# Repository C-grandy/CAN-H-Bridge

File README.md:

# CAN-H-Bridge
A CAN Bus controlled H-Bridge motor driver designed for 12V, 10-20A brushed motors with encoders. Features a Atmel Atmega328 MCU along with a MCP2515 CAN controller for compatability with Arduino or standalone AVR C. 
NOTE: This design should not be used as is, it has a few design flaws as it was a proof of concept that was never developed further. 
## Circuit Overview
The design has two major parts, the controls and the H-Bridge motor driver. 
### Controls
The heart of the control system is the Atmega328 MCU. This MCU communicates over CAN for connectivity to other devices along with sending the appropriate PWM and enable signals to the H-bridge driver. It has connectors for a 2 pin quadrature encoder, specifically designed with GoBilda Yellow Jacket gear motors in mind. 

### Driver
The driver features 2 IRS2104's half-bridge gate drivers to drive the IRF3205 MOSFETS. This is a standard H-bridge setup, with adequete protection for expected loads. 
NOTE: This circuit uses a external 12V refrence for the IRS2104 input voltage, do not exceed 12V on board VCC or the driver might not work correctly. This is a major design flaw in the circuit as it should include a isolated supply that is refrenced off of VCC. 

## PCB Layout:
This board is a 2 layer stackup, with very basic PCB design rules followed. The overall design of the PCB is lacking, the traces are not properly sized for the loads at hand and a lack of copper pours makes this a elementary design. Even with these shortcomings, the PCB works as expected, but in long tests proved it needed refinement. 

Front: 

Back: 

### 3D Render: 

Front:

Back:

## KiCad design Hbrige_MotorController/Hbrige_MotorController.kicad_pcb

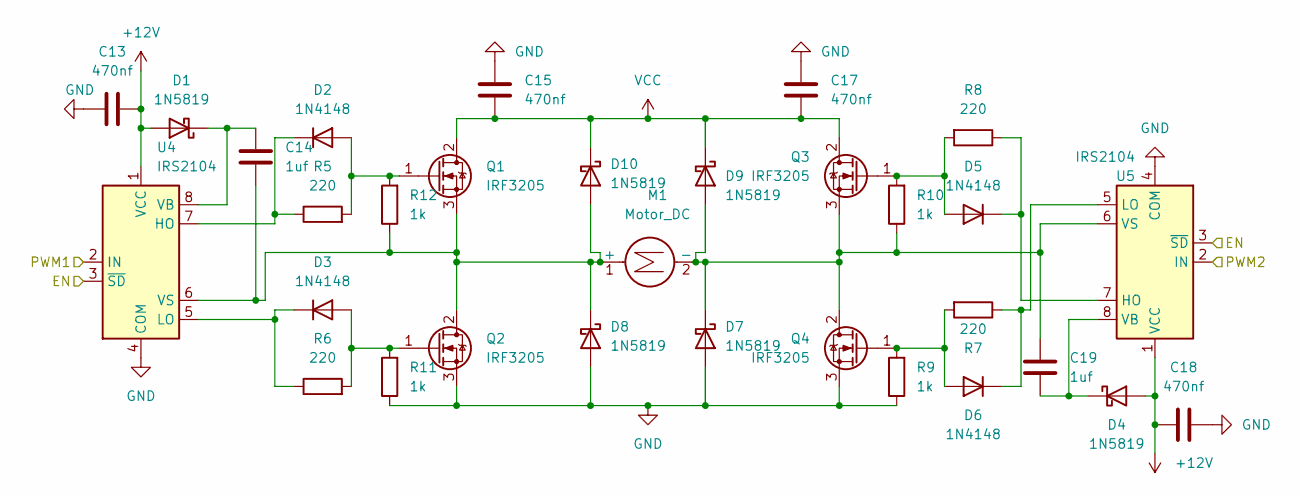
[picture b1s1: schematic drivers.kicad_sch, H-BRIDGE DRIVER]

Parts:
C13, C15, C17, C18: 470nf; C_0603_1608Metric_Pad1.08x0.95mm_HandSolder
C14, C19: 1uf; C_0603_1608Metric_Pad1.08x0.95mm_HandSolder
D1, D4, D7, D8, D9, D10: 1N5819; D_SOD-123
D2, D3, D5, D6: 1N4148; D_SOD-523
M1: Motor_DC; TerminalBlock_Altech_AK300-2_P5.00mm
Q1, Q2, Q3, Q4: IRF3205; TO-220-3_Horizontal_TabDown
R5, R6, R7, R8: 220; R_0603_1608Metric_Pad0.98x0.95mm_HandSolder
R9, R10, R11, R12: 1k; R_0603_1608Metric_Pad0.98x0.95mm_HandSolder
U4, U5: IRS2104; SOIC-8_3.9x4.9mm_P1.27mm

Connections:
+12V: C13.1, C18.2, D1.2 (A), D4.2 (A), U4.1 (VCC), U5.1 (VCC); also elsewhere on the board
/Controls/EN: U4.3 (~SD), U5.3 (~SD); also elsewhere on the board
/Controls/PWM1: U4.2 (IN); also elsewhere on the board
/Controls/PWM2: U5.2 (IN); also elsewhere on the board
GND: C13.2, C15.2, C17.2, C18.1, D7.2 (A), D8.2 (A), Q2.3 (S), Q4.3 (S), R9.1, R11.1, U4.4 (COM), U5.4 (COM); also elsewhere on the board
unnamed: C14.1, D1.1 (K), U4.8 (VB)
unnamed: C14.2, D8.1 (K), D10.2 (A), M1.1 (+), Q1.3 (S), Q2.2 (D), R12.1, U4.6 (VS)
unnamed: C19.1, D4.1 (K), U5.8 (VB)
unnamed: C19.2, D7.1 (K), D9.2 (A), M1.2 (-), Q3.3 (S), Q4.2 (D), R10.1, U5.6 (VS)
unnamed: D2.1 (K), R5.1, U4.7 (HO)
unnamed: D2.2 (A), Q1.1 (G), R5.2, R12.2
unnamed: D3.1 (K), R6.1, U4.5 (LO)
unnamed: D3.2 (A), Q2.1 (G), R6.2, R11.2
unnamed: D5.1 (K), R8.1, U5.7 (HO)
unnamed: D5.2 (A), Q3.1 (G), R8.2, R10.2
unnamed: D6.1 (K), R7.1, U5.5 (LO)
unnamed: D6.2 (A), Q4.1 (G), R7.2, R9.2
VCC: C15.1, C17.1, D9.1 (K), D10.1 (K), Q1.2 (D), Q3.2 (D); also elsewhere on the board

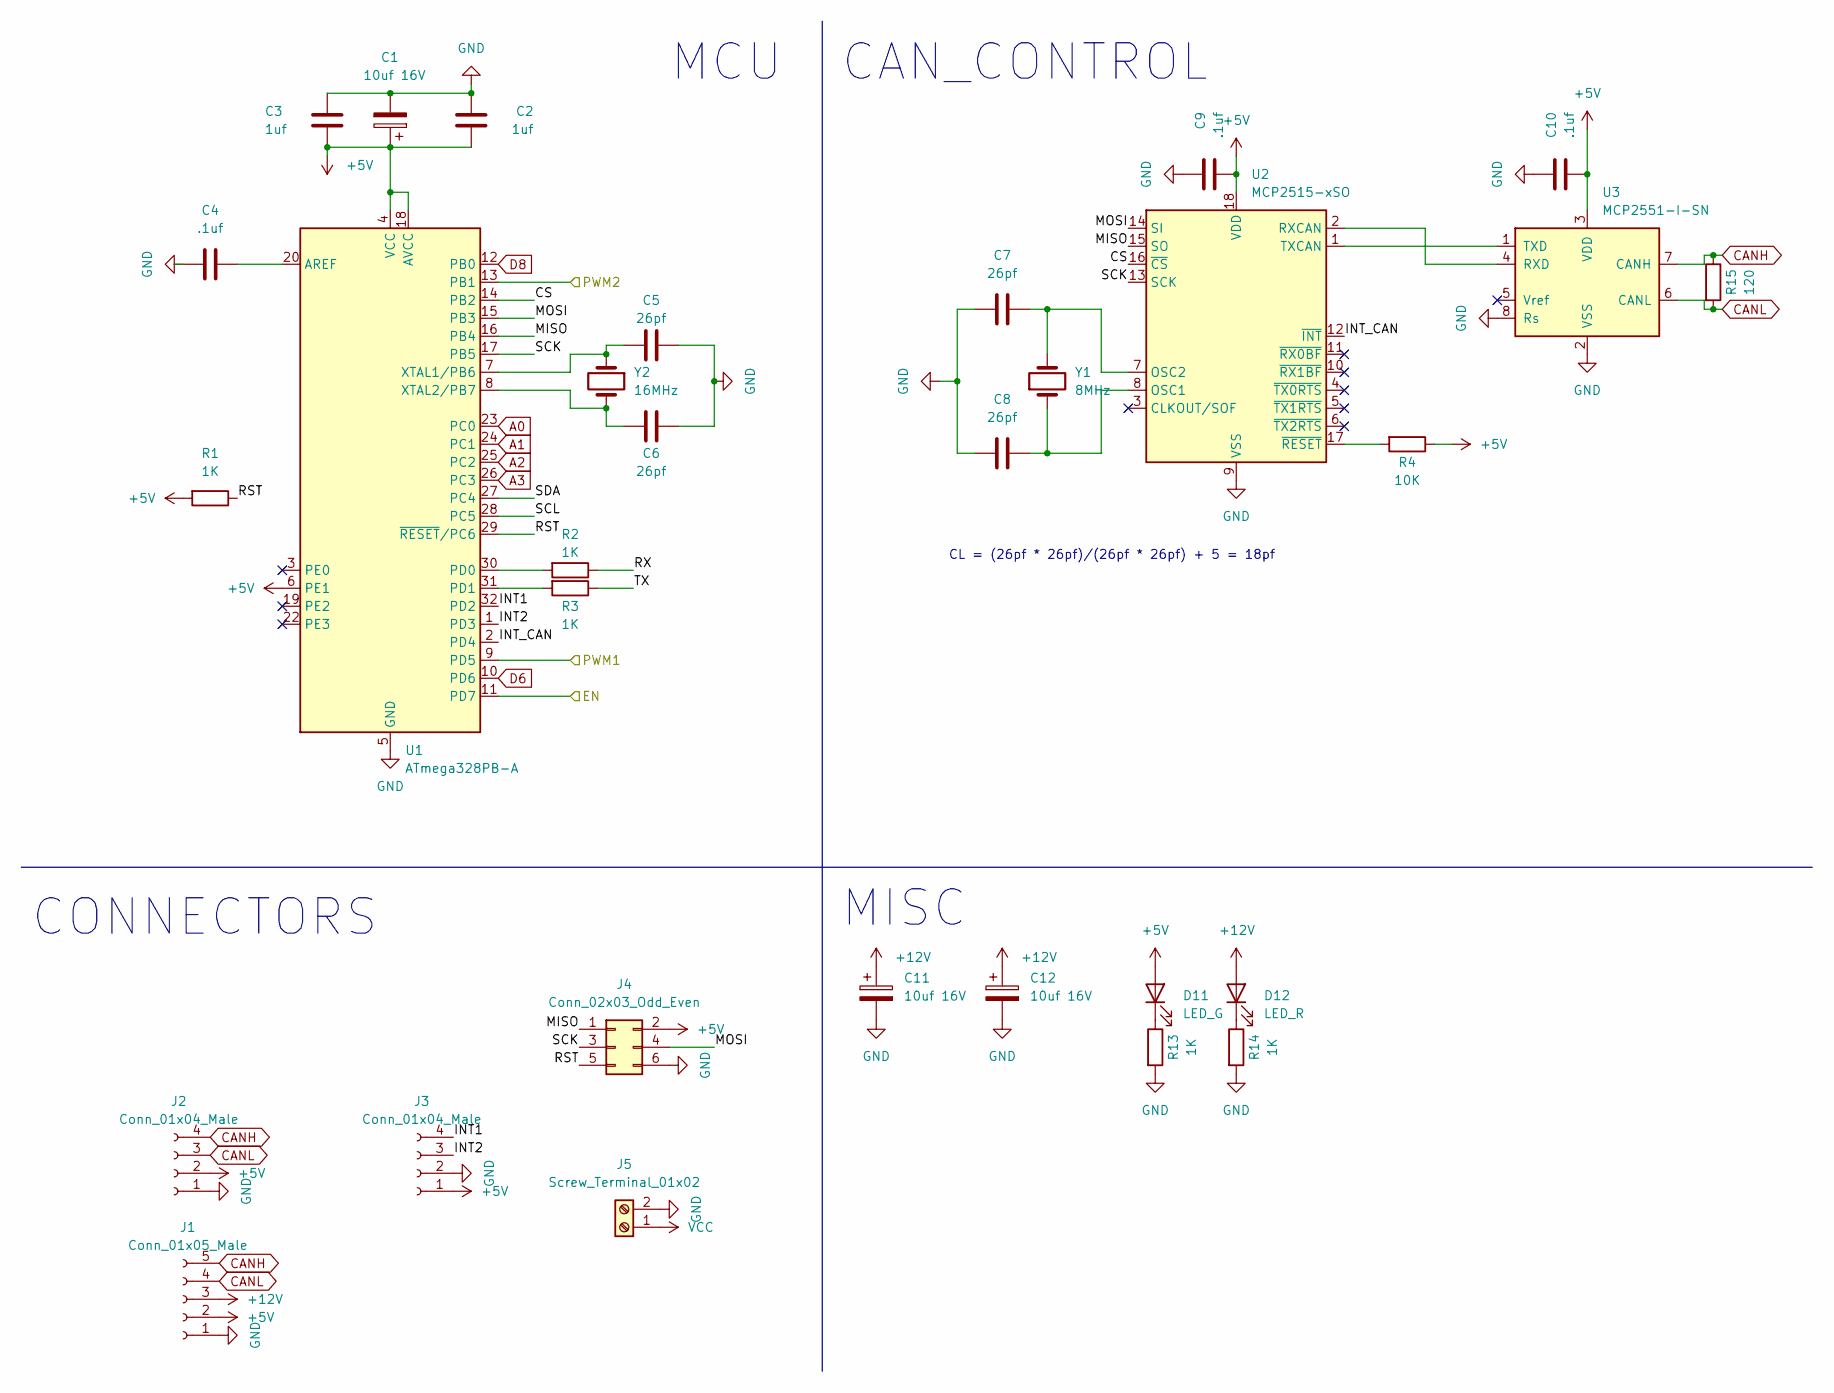
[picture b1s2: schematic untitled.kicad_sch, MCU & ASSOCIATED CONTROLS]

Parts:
C1, C11, C12: 10uf 16V; CP_Radial_D5.0mm_P2.00mm
C2, C3: 1uf; C_0603_1608Metric_Pad1.08x0.95mm_HandSolder
C4, C9, C10: .1uf; C_0603_1608Metric_Pad1.08x0.95mm_HandSolder
C5, C6, C7, C8: 26pf; C_0603_1608Metric_Pad1.08x0.95mm_HandSolder
D11: LED_G; LED_0603_1608Metric_Pad1.05x0.95mm_HandSolder
D12: LED_R; LED_0603_1608Metric_Pad1.05x0.95mm_HandSolder
J1: Conn_01x05_Male; JST_XH_B5B-XH-A_1x05_P2.50mm_Vertical
J2, J3: Conn_01x04_Male; JST_XA_B04B-XASK-1-A_1x04_P2.50mm_Vertical
J4: Conn_02x03_Odd_Even; PinHeader_2x03_P2.54mm_Vertical
J5: Screw_Terminal_01x02; TerminalBlock_Altech_AK300-2_P5.00mm
R1, R2, R3, R13, R14: 1K; R_0603_1608Metric_Pad0.98x0.95mm_HandSolder
R4: 10K; R_0603_1608Metric_Pad0.98x0.95mm_HandSolder
R15: 120; R_0603_1608Metric_Pad0.98x0.95mm_HandSolder
U1: ATmega328PB-A; TQFP-32_7x7mm_P0.8mm
U2: MCP2515-xSO; SOIC-18W_7.5x11.6mm_P1.27mm
U3: MCP2551-I-SN; SOIC-8_3.9x4.9mm_P1.27mm
Y1: 8MHz; Crystal_SMD_5032-2Pin_5.0x3.2mm
Y2: 16MHz; Crystal_SMD_5032-2Pin_5.0x3.2mm

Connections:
+5V: C1.1, C2.2, C3.1, C9.2, C10.2, D11.2 (A), J1.2, J2.2, J3.1, J4.2, R1.2, R4.1, U1.4 (VCC), U1.6 (PE1), U1.18 (AVCC), U2.18 (VDD), U3.3 (VDD)
+12V: C11.1, C12.1, D12.2 (A), J1.3; also elsewhere on the board
/Controls/CS: U1.14 (PB2), U2.16 (~CS)
/Controls/EN: U1.11 (PD7); also elsewhere on the board
/Controls/INT1: J3.4, U1.32 (PD2)
/Controls/INT2: J3.3, U1.1 (PD3)
/Controls/INT_CAN: U1.2 (PD4), U2.12 (~INT)
/Controls/MISO: J4.1, U1.16 (PB4), U2.15 (SO)
/Controls/MOSI: J4.4, U1.15 (PB3), U2.14 (SI)
/Controls/PWM1: U1.9 (PD5); also elsewhere on the board
/Controls/PWM2: U1.13 (PB1); also elsewhere on the board
/Controls/RST: J4.5, R1.1, U1.29 (~RESET/PC6)
/Controls/RX: R2.1
/Controls/SCK: J4.3, U1.17 (PB5), U2.13 (SCK)
/Controls/SCL: U1.28 (PC5)
/Controls/SDA: U1.27 (PC4)
/Controls/TX: R3.1
A0: U1.23 (PC0)
A1: U1.24 (PC1)
A2: U1.25 (PC2)
A3: U1.26 (PC3)
CANH: J1.5, J2.4, R15.1, U3.7 (CANH)
CANL: J1.4, J2.3, R15.2, U3.6 (CANL)
D6: U1.10 (PD6)
D8: U1.12 (PB0)
GND: C1.2, C2.1, C3.2, C4.1, C5.1, C6.1, C7.1, C8.1, C9.1, C10.1, C11.2, C12.2, J1.1, J2.1, J3.2, J4.6, J5.2, R13.2, R14.2, U1.5 (GND), U1.21 (GND), U2.9 (VSS), U3.2 (VSS), U3.8 (Rs); also elsewhere on the board
unnamed: C4.2, U1.20 (AREF)
unnamed: C5.2, U1.7 (XTAL1/PB6), Y2.1
unnamed: C6.2, U1.8 (XTAL2/PB7), Y2.2
unnamed: C7.2, U2.7 (OSC2), Y1.2
unnamed: C8.2, U2.8 (OSC1), Y1.1
unnamed: D11.1 (K), R13.1
unnamed: D12.1 (K), R14.1
unnamed: R2.2, U1.30 (PD0)
unnamed: R3.2, U1.31 (PD1)
unnamed: R4.2, U2.17 (~RESET)
unnamed: U2.1 (TXCAN), U3.1 (TXD)
unnamed: U2.2 (RXCAN), U3.4 (RXD)
VCC: J5.1; also elsewhere on the board

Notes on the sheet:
MCU
CONNECTORS
CL = (26pf * 26pf)/(26pf * 26pf) + 5 = 18pf
CAN_CONTROL
MISC

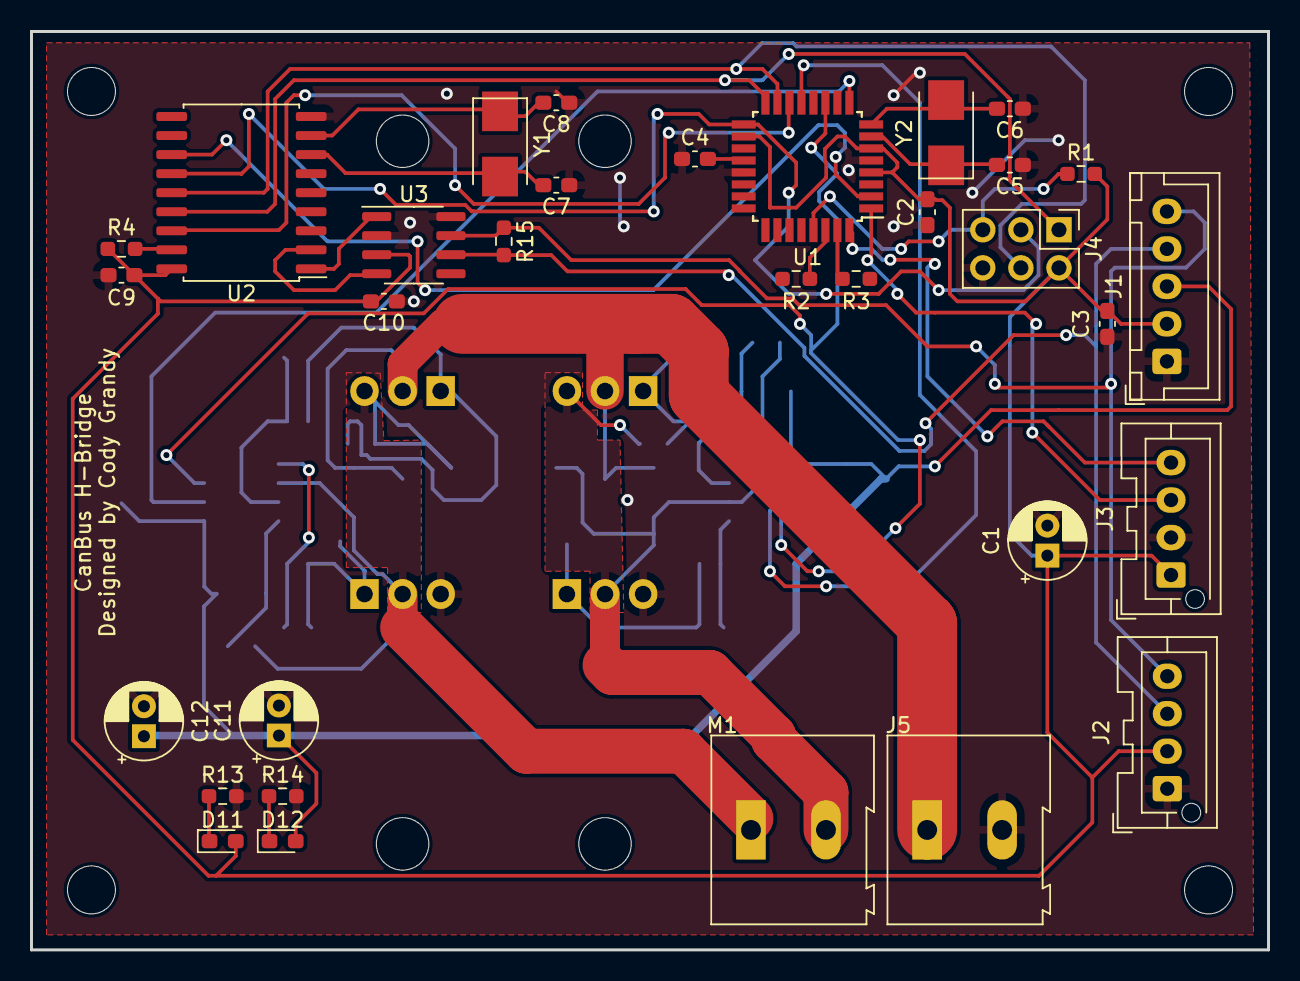
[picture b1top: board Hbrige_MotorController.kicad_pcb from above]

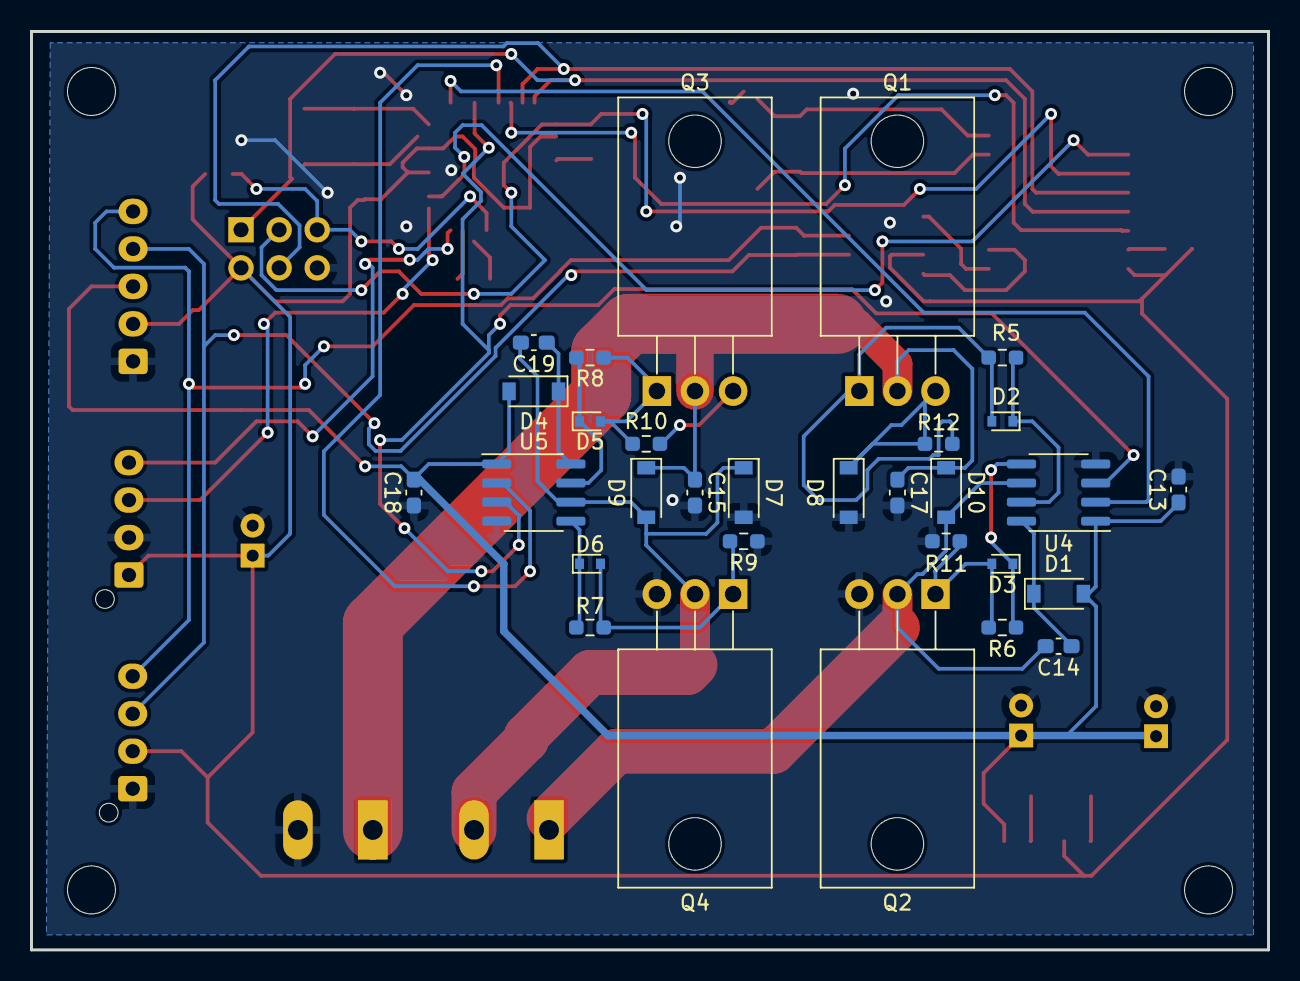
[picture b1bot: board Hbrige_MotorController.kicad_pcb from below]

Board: 2 copper layers, 82.5 x 61.2 mm, 62 parts (30 on the bottom side), 41 nets.

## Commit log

2025-09-18 Create d
